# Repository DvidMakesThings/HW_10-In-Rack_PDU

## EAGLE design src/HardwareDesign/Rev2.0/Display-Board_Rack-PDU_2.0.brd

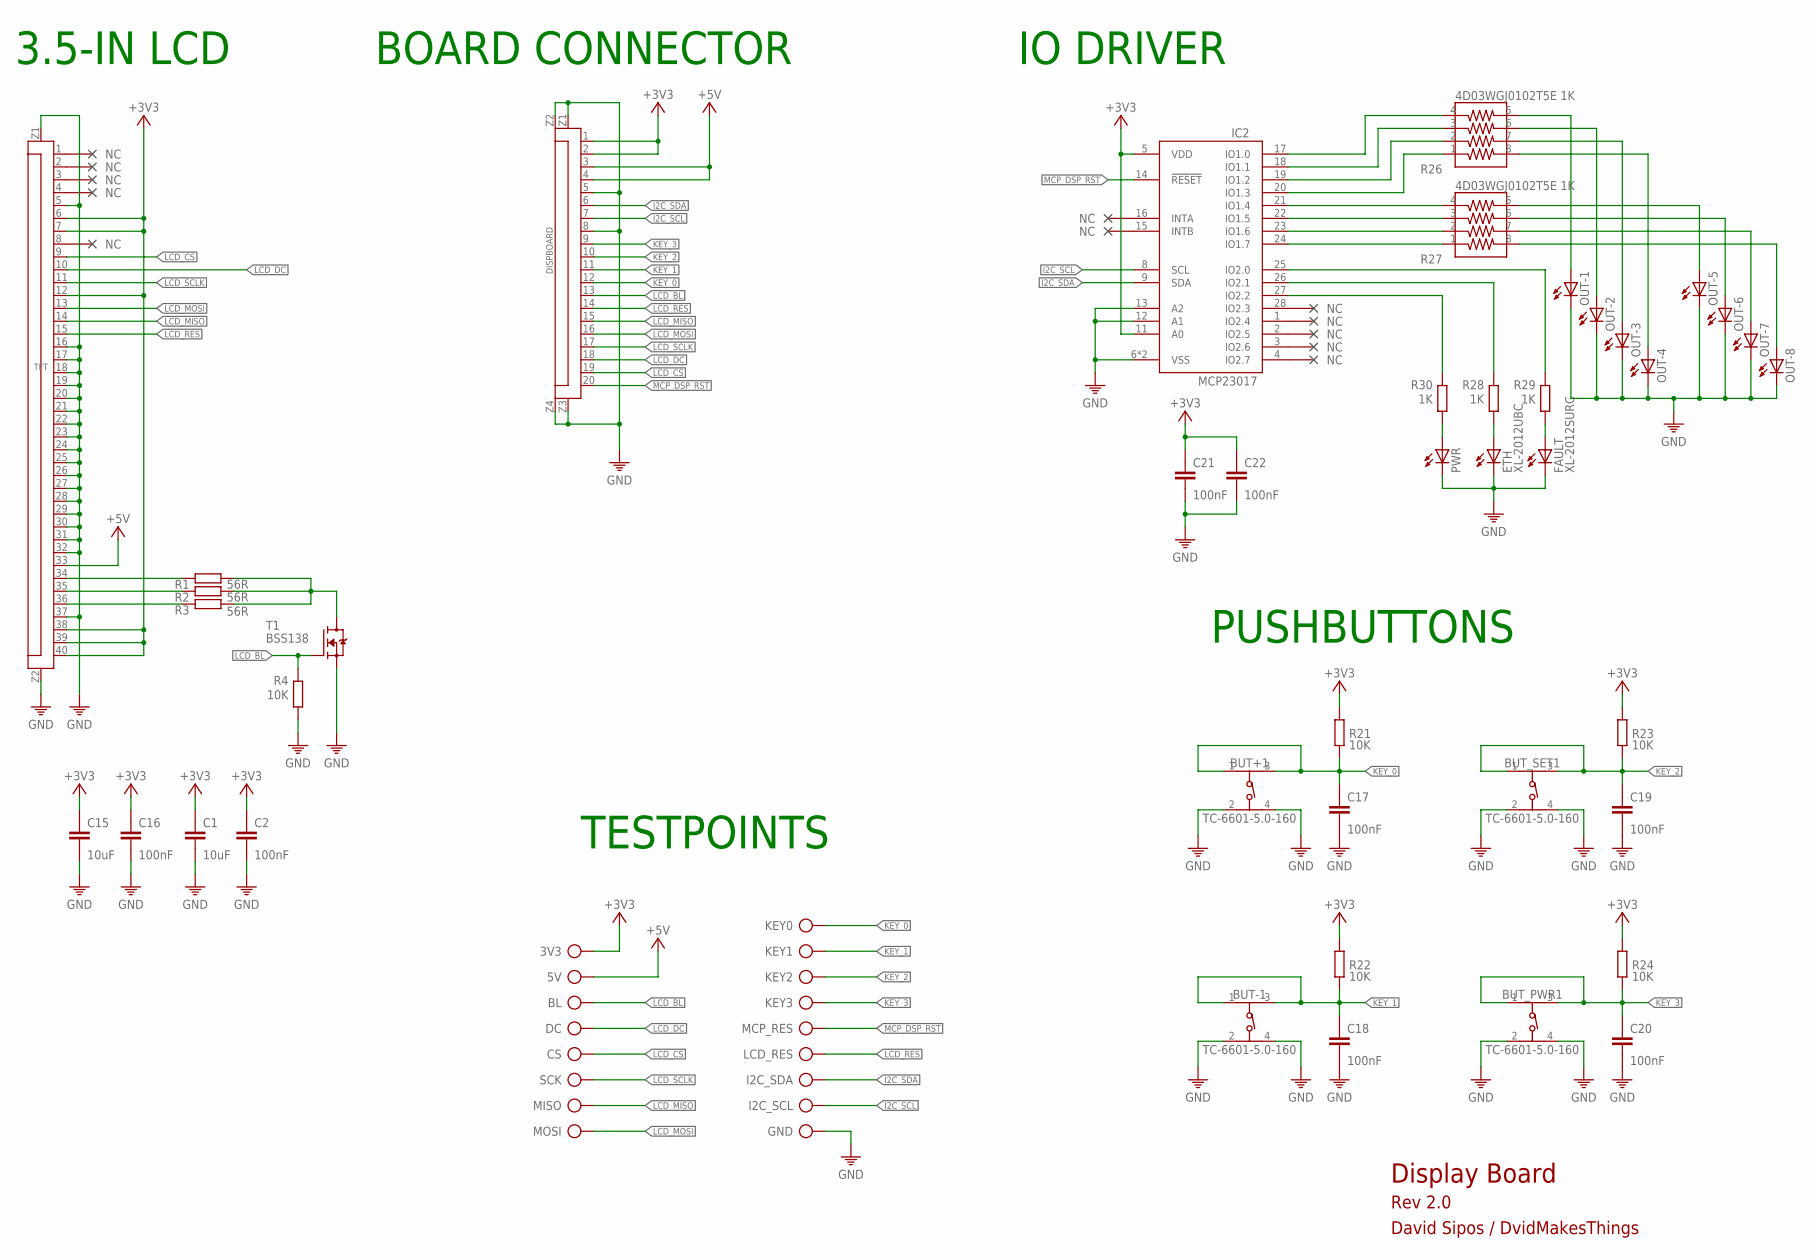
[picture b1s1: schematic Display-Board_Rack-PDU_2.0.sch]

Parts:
3V3, 5V: TP
BL: TP
BUT+1: TC-6601-5.0-160; 430182043816
BUT-1: TC-6601-5.0-160; 430182043816
BUT_PWR1: TC-6601-5.0-160; 430182043816
BUT_SET1: TC-6601-5.0-160; 430182043816
C1, C15: 10uF; C0402
C2, C16, C17, C18, C19, C20, C21, C22: 100nF; C0402
CS: TP
DC: TP
DISPBOARD: FPC20-H; FPC20
ETH: XL-2012UBC; CHIP-LED0805
FAULT: XL-2012SURC; CHIP-LED0805
GND: TP
I2C_SCL, I2C_SDA: TP
IC2: MCP23017-E/ML; QFN28[6X6]ML
KEY0, KEY1, KEY2, KEY3: TP
LCD_RES: TP
MCP_RES: TP
MISO: TP
MOSI: TP
OUT-1, OUT-2, OUT-3, OUT-4, OUT-5, OUT-6, OUT-7, OUT-8: LEDCHIP-LED0805; CHIP-LED0805
PWR: LEDCHIP-LED0805; CHIP-LED0805
R1, R2, R3: 56R; 0402
R4, R21, R22, R23, R24: 10K; 0402
R26, R27: 4D03WGJ0102T5E 1K; 742C083103JP
R28, R29, R30: 1K; 0402
SCK: TP
T1: BSS138; SOT23
TFT: FPC40-HD; FPC40_3.5TFT

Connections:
+3V3: 3V3.TP, C1.1, C2.1, C15.1, C16.1, C21.1, C22.1, DISPBOARD.1, DISPBOARD.2, IC2.5 (VDD), IC2.11 (A0), R21.1, R22.1, R23.1, R24.1, TFT.6, TFT.7, TFT.12, TFT.38, TFT.39, TFT.40
+5V: 5V.TP, DISPBOARD.3, DISPBOARD.4, TFT.33
GND: BUT+1.2, BUT+1.4, BUT-1.2, BUT-1.4, BUT_PWR1.2, BUT_PWR1.4, BUT_SET1.2, BUT_SET1.4, C1.2, C2.2, C15.2, C16.2, C17.2, C18.2, C19.2, C20.2, C21.2, C22.2, DISPBOARD.5, DISPBOARD.8, DISPBOARD.Z1, DISPBOARD.Z2, DISPBOARD.Z3, DISPBOARD.Z4, ETH.C, FAULT.C, GND.TP, IC2.6 (VSS), IC2.12 (A1), IC2.13 (A2), IC2.PAD (VSS), OUT-1.C, OUT-2.C, OUT-3.C, OUT-4.C, OUT-5.C, OUT-6.C, OUT-7.C, OUT-8.C, PWR.C, R4.2, T1.2 (S), TFT.5, TFT.16, TFT.17, TFT.18, TFT.19, TFT.20, TFT.21, TFT.22, TFT.23, TFT.24, TFT.25, TFT.26, TFT.27, TFT.28, TFT.29, TFT.30, TFT.31, TFT.32, TFT.37, TFT.Z1, TFT.Z2
I2C0_SCL: DISPBOARD.7, I2C_SCL.TP, IC2.8 (SCL)
I2C0_SDA: DISPBOARD.6, I2C_SDA.TP, IC2.9 (SDA)
KEY_0: BUT+1.1, BUT+1.3, C17.1, DISPBOARD.12, KEY0.TP, R21.2
KEY_1: BUT-1.1, BUT-1.3, C18.1, DISPBOARD.11, KEY1.TP, R22.2
KEY_2: BUT_SET1.1, BUT_SET1.3, C19.1, DISPBOARD.10, KEY2.TP, R23.2
KEY_3: BUT_PWR1.1, BUT_PWR1.3, C20.1, DISPBOARD.9, KEY3.TP, R24.2
LCD_BL: BL.TP, DISPBOARD.13, R4.1, T1.1 (G)
LCD_CS: CS.TP, DISPBOARD.19, TFT.9
LCD_DC: DC.TP, DISPBOARD.18, TFT.10
LCD_MISO: DISPBOARD.15, MISO.TP, TFT.14
LCD_MOSI: DISPBOARD.16, MOSI.TP, TFT.13
LCD_RES: DISPBOARD.14, LCD_RES.TP, TFT.15
LCD_SCLK: DISPBOARD.17, SCK.TP, TFT.11
MCP_LCD_RST: DISPBOARD.20, IC2.14 (!RESET), MCP_RES.TP
unnamed: R2.2, TFT.35
unnamed: R3.2, TFT.36
unnamed: R1.1, R2.1, R3.1, T1.3 (D)
unnamed: R1.2, TFT.34
unnamed: IC2.26 (IO2.1), R28.1
unnamed: IC2.27 (IO2.2), R30.1
unnamed: IC2.25 (IO2.0), R29.1
unnamed: IC2.17 (IO1.0), R26.4
unnamed: IC2.18 (IO1.1), R26.3
unnamed: IC2.19 (IO1.2), R26.2
unnamed: IC2.20 (IO1.3), R26.1
unnamed: IC2.21 (IO1.4), R27.4
unnamed: IC2.22 (IO1.5), R27.3
unnamed: IC2.23 (IO1.6), R27.2
unnamed: IC2.24 (IO1.7), R27.1
unnamed: OUT-1.A, R26.5
unnamed: OUT-2.A, R26.6
unnamed: OUT-3.A, R26.7
unnamed: OUT-4.A, R26.8
unnamed: OUT-5.A, R27.5
unnamed: OUT-6.A, R27.6
unnamed: OUT-7.A, R27.7
unnamed: OUT-8.A, R27.8
unnamed: FAULT.A, R29.2
unnamed: ETH.A, R28.2
unnamed: PWR.A, R30.2

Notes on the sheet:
BOARD CONNECTOR
3.5-IN LCD
PUSHBUTTONS
IO DRIVER
Display Board
Rev 2.0
David Sipos / DvidMakesThings
TESTPOINTS

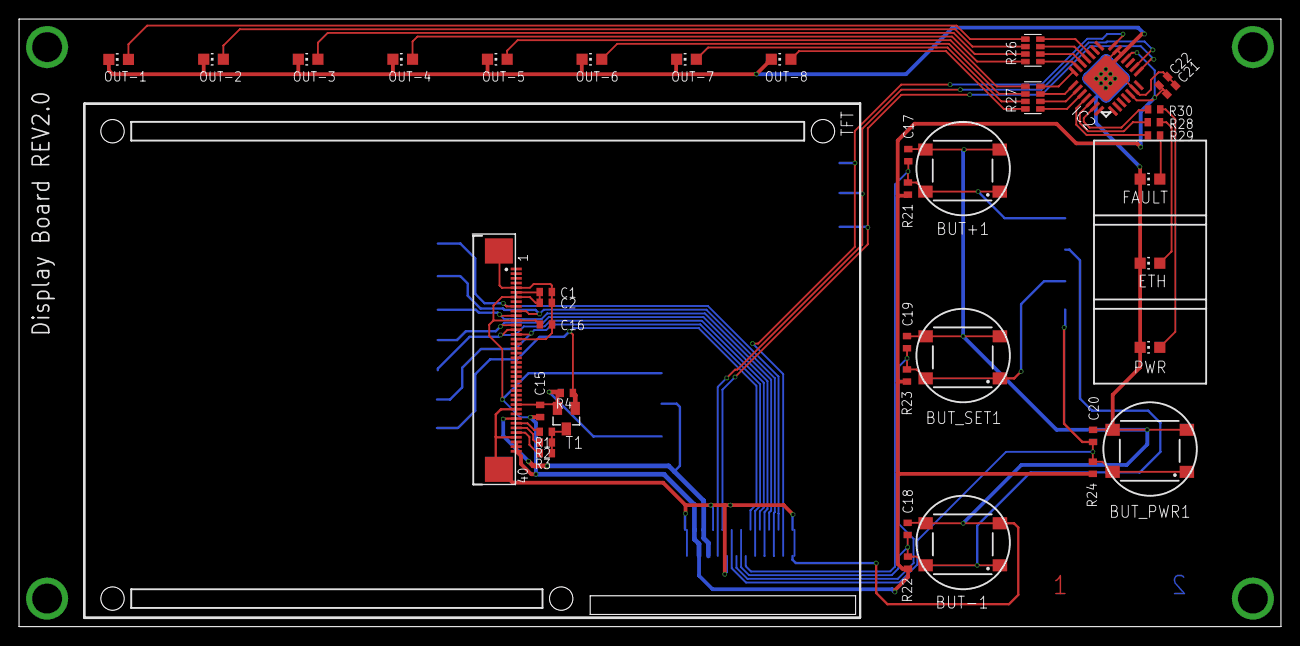
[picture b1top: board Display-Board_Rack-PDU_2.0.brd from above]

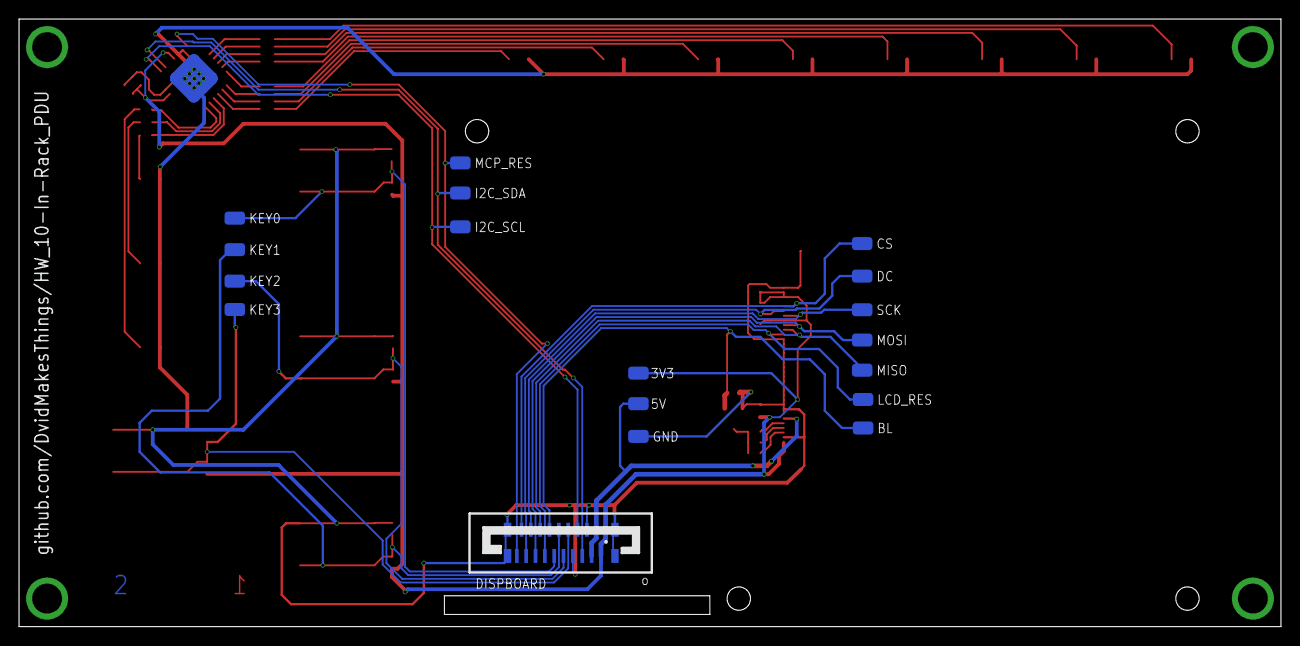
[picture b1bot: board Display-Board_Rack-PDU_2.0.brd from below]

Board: 2 copper layers, 135.0 x 65.0 mm, 60 parts (18 on the bottom side), 43 nets.

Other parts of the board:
U$1: 2-LAYER

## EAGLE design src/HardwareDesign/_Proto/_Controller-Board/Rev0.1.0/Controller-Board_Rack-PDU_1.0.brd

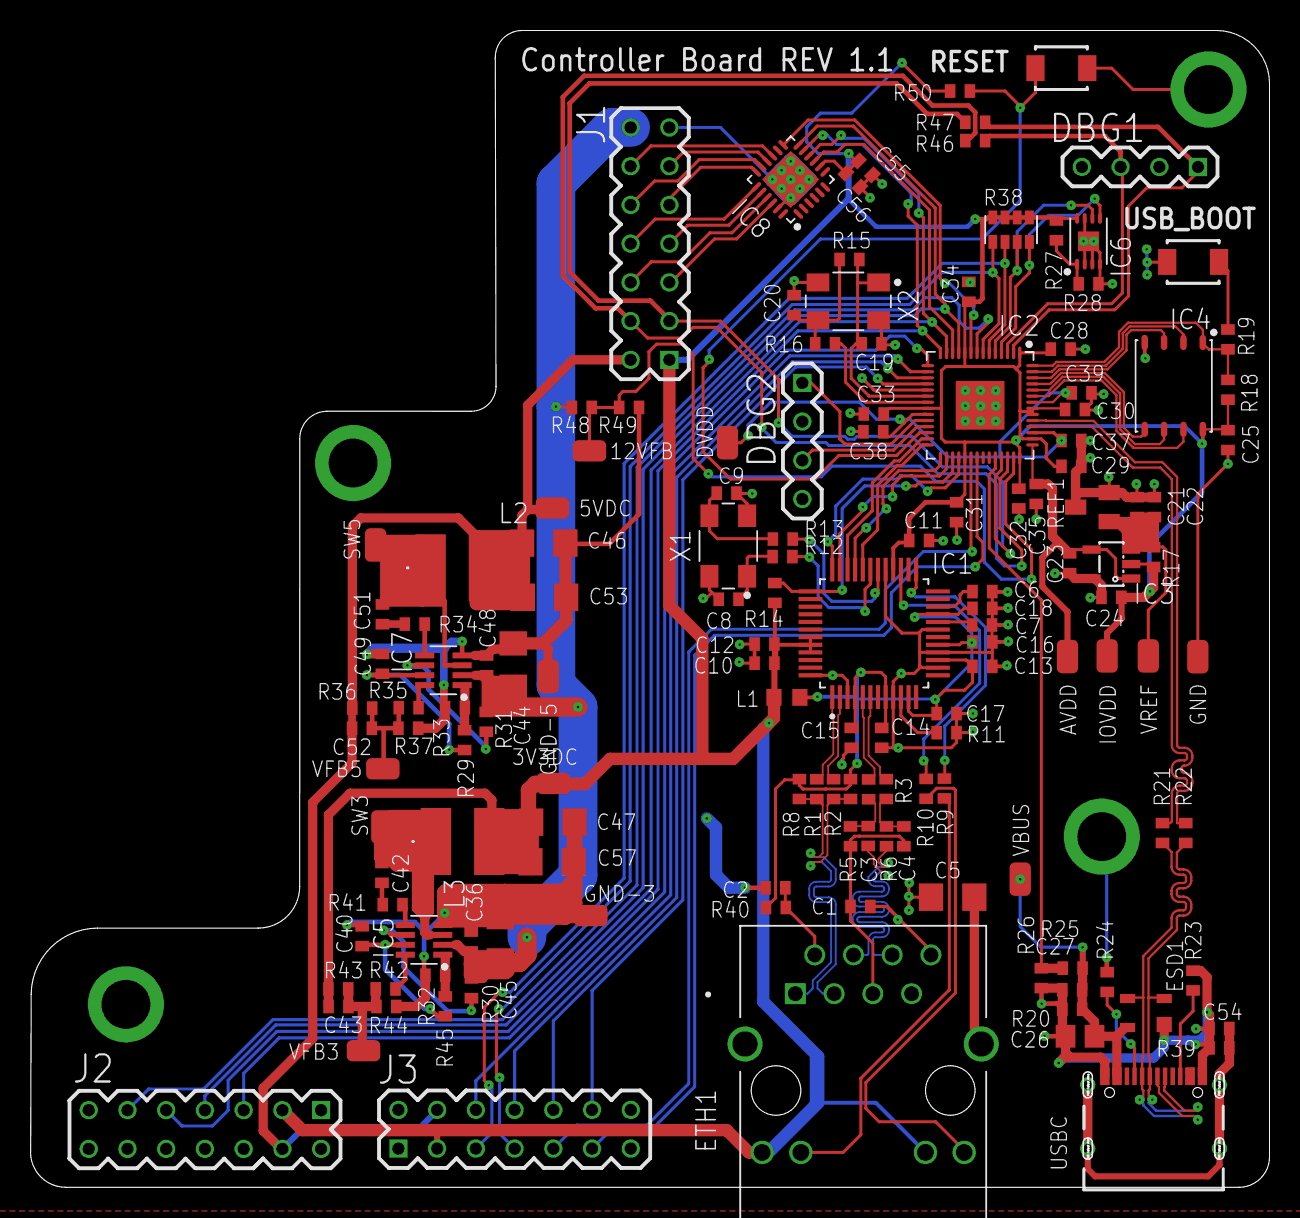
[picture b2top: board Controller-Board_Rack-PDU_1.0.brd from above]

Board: 4 copper layers, 81.3 x 75.9 mm, 144 parts (0 on the bottom side), 106 nets.

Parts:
3V3DC, 5VDC, 12VFB: TP
AVDD: TP
C1, C6, C10, C11, C12, C13, C14, C15, C16, C17, C18, C22, C23, C24, C25, C28, C29, C30, C31, C32, C33, C34, C35, C37, C38, C39, C55, C56: 100nF; C0402
C2: 22nF; C0402
C3, C4: 6.8nF; C0402
C5: C1206C102KGRACTM; C1206
C7: 4.7uF; C0402
C8, C9: 18pF; C0402
C19, C20: 15pF; C0402
C21: 1uF; C0402
C26: 10uF; 0805
C27, C36, C40, C42, C48, C49, C51: 100nF; 0402
C43, C52: 33pF; 0402
C44, C45: CL31A226KAHNNNE - 22uF 25V; C1206
C46, C47, C53, C57: CL31A226KPHNNNE - 22uF - 10V; C1206
C54: 4.7nF; 0402
DBG1, DBG2: 1X4
DVDD: TP
ESD1: SP0503BAHTG-ES; SOT143
ETH1: SI-60118-F; RJ45-CAT5
GND: TP
GND-3, GND-5: TP
IC1: W5500; LQFP48
IC2: RP2040; QFN40P700X700X100-57T510
IC3: MCP6001R; SOT23-5
IC4: W25Q128JVPIQ; SON127P600X500X75-8N
IC5: MP2315S; SOT65P280X110-8N
IC6: CAT24C256HU4IGT3; SON50P300X200X50-9T130X140N
IC7: MP2315GJ-Z; SOT65P280X110-8N
IC8: MCP23S18-E/MJ; QFN50P400X400X100-25T265
IOVDD: TP
J1, J2, J3: 2X7
L1: BLM18EG221TN1D; 0603
L2: 4.9uH; SRR5228A
L3: 4.2uH; SRR5228A
R1, R2, R3, R4: 3.3R; 0402
R5, R6: 49.9R; C0402
R7, R8: 49.9R; 0402
R9, R10, R40: 470R; 0402
R11: 12.4K 1%; 0402
R12, R15, R46, R47: 0R; 0402
R13, R39: 1M; 0402
R14, R17, R27, R28: 4.7K; 0402
R16, R19: 1K; 0402
R18: DNI; 0402
R20: 2.2K 1%; 0402
R21, R22: 27R; 0402
R23, R24: 5.1K; 0402
R25, R26, R49, R50: 10K; 0402
R29, R45, R48: 100K; 0402
R30, R31: 499K; 0402
R32, R37: 7.5K; 0402
R33: 9.09K; 0402
R34, R41: 10R; 0402
R35: 20K; 0402
R36, R43: 40.2K; 0402
R38: 4D03WGJ0332T5E; 742C083103JP
R42: 33K; 0402
R44: 12.7K; 0402
REF1: LM4040BXX; SOT23
RESET: B3U-1000P-B; SWITCH-OMRON_B3U-1000P
SW3, SW5: TP
USBC: USB-TYPE-C-018; 629722000214
USB_BOOT: B3U-1000P-B; SWITCH-OMRON_B3U-1000P
VBUS: TP
VFB3, VFB5: TP
VREF: TP
X1: XC53M4-25.000-F18NJDTL; OSCCC500X320X130
X2: K5A1200015304P; OSCCC500X320X130

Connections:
!ACT: IC1.27, R10.1
!INT: IC1.36, IC2.32
!LINK: IC1.25, R9.1
!QSPI_SS: IC2.56, IC4.1, R18.1, R19.2
!RST: IC1.37, IC2.31, R14.1
!SPI0_CS: IC1.32, IC2.28
!SPI1_CS: IC2.12, IC8.9
!SPI1_CS_S: IC2.8, J2.11
+1V1: C37.1, C38.1, C39.1, DVDD.TP, IC2.23, IC2.45, IC2.50
+3V3: 3V3DC.TP, C10.1, C11.1, C12.1, C24.1, C25.1, C28.1, C29.1, C30.1, C31.1, C32.1, C33.1, C34.1, C43.1, C47.1, C55.1, C56.1, C57.1, ETH1.9, ETH1.11, IC1.28, IC1.43, IC1.44, IC1.45, IC2.1, IC2.10, IC2.22, IC2.33, IC2.42, IC2.44, IC2.48, IC2.49, IC3.2, IC4.8, IC6.8, IC8.8, IOVDD.TP, J1.1, J2.3, J3.3, L1.1, L3.2, R14.2, R17.2, R18.2, R27.2, R38.5, R38.6, R38.7, R38.8, R43.1, R50.1
+3V3_A: C13.1, C14.1, C15.1, C16.1, C17.1, C18.1, IC1.4, IC1.8, IC1.11, IC1.15, IC1.17, IC1.21, L1.2, R7.2, R8.2, R40.2
+5V: 5VDC.TP, C46.1, C52.1, C53.1, J1.2, J2.4, J3.4, L2.2, R36.1
+12V: C36.1, C44.1, C45.1, C48.1, IC5.2, IC7.2, J1.14, R30.1, R31.1, R48.2
AVDD: AVDD.TP, C23.1, C35.1, IC2.43, IC3.1, IC3.4
CC1: R24.1, USBC.A5
CC2: R23.1, USBC.B5
CHASSIS: C5.2, ETH1.S1, ETH1.S2
DIO_RESET: IC2.9, IC8.13
DP_N: ESD1.3, R21.1, USBC.A7, USBC.B7
DP_P: ESD1.2, R22.1, USBC.A6, USBC.B6
DSP_RES: IC2.34, J3.9
EXP_RST: IC2.35, J3.11
GND: C1.2, C2.2, C5.1, C6.2, C7.2, C8.2, C9.2, C10.2, C11.2, C12.2, C13.2, C14.2, C15.2, C16.2, C17.2, C18.2, C19.2, C20.2, C21.2, C22.2, C23.2, C24.2, C25.2, C26.2, C27.2, C28.2, C29.2, C30.2, C31.2, C32.2, C33.2, C34.2, C35.2, C36.2, C37.2, C38.2, C39.2, C40.2, C44.2, C45.2, C46.2, C47.2, C48.2, C49.2, C53.2, C54.2, C55.2, C56.2, C57.2, DBG1.2, DBG1.4, DBG2.2, DBG2.4, ESD1.1, ETH1.8, GND.TP, GND-3.TP, GND-5.TP, IC1.3, IC1.9, IC1.14, IC1.16, IC1.19, IC1.29, IC1.48, IC2.19, IC2.57, IC3.5, IC4.4, IC5.4, IC6.2, IC6.3, IC6.4, IC6.7, IC6.9, IC7.4, IC8.23, IC8.25, J1.13, J2.1, J2.2, J2.13, J2.14, J3.1, J3.2, J3.13, J3.14, R11.1, R20.2, R23.2, R24.2, R26.2, R28.1, R32.2, R33.2, R37.2, R39.2, R44.2, R49.1, REF1.2, REF1.3, RESET.2, USBC.A1, USBC.A12, USBC.B1, USBC.B12, USB_BOOT.2, X1.2, X1.4, X2.2, X2.4
I2C0_SCL: IC2.7, J3.7, R38.1
I2C0_SDA: IC2.6, J3.5, R38.2
I2C1_SCL: IC2.5, IC6.6, R38.3
I2C1_SDA: IC2.4, IC6.5, R38.4
I_MEA/TX: IC2.40, J1.4, R46.1
KEY_0: IC2.15, J3.6
KEY_1: IC2.16, J3.8
KEY_2: IC2.17, J3.10
KEY_3: IC2.18, J3.12
unnamed: IC1.10, R11.2
unnamed: ETH1.10, R9.2
unnamed: ETH1.12, R10.2
unnamed: C6.1, IC1.22
unnamed: C7.1, IC1.20
unnamed: C8.1, R12.1, X1.1
unnamed: C9.1, R13.1, X1.3
unnamed: IC1.31, R12.2
unnamed: IC1.30, R13.2
unnamed: IC5.5, R41.2
unnamed: IC5.1, R32.1, R45.2
unnamed: IC7.1, R29.2, R33.1
unnamed: C20.1, R15.2, R16.1, X2.3
unnamed: IC7.6, R31.2
unnamed: C49.1, IC7.7, R29.1
unnamed: IC2.26, R50.2, RESET.1
unnamed: IC5.8, R42.1
unnamed: C42.2, IC5.3, L3.1, SW3.TP
unnamed: C42.1, R41.1
unnamed: IC6.1, R27.1, R28.2
unnamed: C43.2, R42.2, R43.2, R44.1, VFB3.TP
unnamed: IC5.6, R30.2
unnamed: C40.1, IC5.7, R45.1
unnamed: IC7.5, R34.2
unnamed: IC7.8, R35.1
unnamed: C51.2, IC7.3, L2.1, SW5.TP
unnamed: C51.1, R34.1
unnamed: C52.2, R35.2, R36.2, R37.1, VFB5.TP
PWR_DETECT: 12VFB.TP, IC2.41, R48.1, R49.2
QSPI_SCLK: IC2.52, IC4.6
QSPI_SD0: IC2.53, IC4.5
QSPI_SD1: IC2.55, IC4.2
QSPI_SD2: IC2.54, IC4.3
QSPI_SD3: IC2.51, IC4.7
RCT: C1.1, ETH1.5, R5.1, R6.1
RDC_RD_N: C3.1, R4.2, R5.2
RDC_RD_P: C4.1, R3.2, R6.2
RD_N: C3.2, ETH1.6
RD_P: C4.2, ETH1.4
REL_0: IC8.15, J1.12
REL_1: IC8.16, J1.11
REL_2: IC8.17, J1.10
REL_3: IC8.18, J1.9
REL_4: IC8.19, J1.8
REL_5: IC8.20, J1.7
REL_6: IC8.21, J1.6
REL_7: IC8.22, J1.5
RP_XI: C19.1, IC2.20, R15.1, X2.1
RP_XO: IC2.21, R16.2
RX_RD_N: IC1.5, R4.1
RX_RD_P: IC1.6, R3.1
SPI0_MISO: IC1.34, IC2.27
SPI0_MOSI: IC1.35, IC2.30
SPI0_SCK: IC1.33, IC2.29
SPI1_MISO: IC2.11, IC8.12, J2.7
SPI1_MOSI: IC2.14, IC8.11, J2.5
SPI1_SCK: IC2.13, IC8.10, J2.9
SWCLK: DBG2.1, IC2.24
SWDIO: DBG2.3, IC2.25
TCT: C2.1, ETH1.2, R40.1
TD_N: ETH1.3, R1.2, R8.1
TD_P: ETH1.1, R2.2, R7.1
TX_TD_N: IC1.1, R1.1
TX_TD_P: IC1.2, R2.1
UART0_RX: DBG1.1, IC2.2, R47.2
UART0_TX: DBG1.3, IC2.3, R46.2
USB_BOOT: R19.1, USB_BOOT.1
USB_DP_N: IC2.46, R21.2
USB_DP_P: IC2.47, R22.2
USB_SHIELD: C54.1, R39.1, USBC.S1, USBC.S2, USBC.S3, USBC.S4
VBUS: C26.1, C27.1, ESD1.4, R20.1, R25.1, USBC.A4, USBC.A9, USBC.B4, USBC.B9, VBUS.TP
VREF: C21.1, C22.1, IC3.3, R17.1, REF1.1, VREF.TP
V_MEA/RX: IC2.39, J1.3, R47.1
V_USB: IC2.38, R25.2, R26.1

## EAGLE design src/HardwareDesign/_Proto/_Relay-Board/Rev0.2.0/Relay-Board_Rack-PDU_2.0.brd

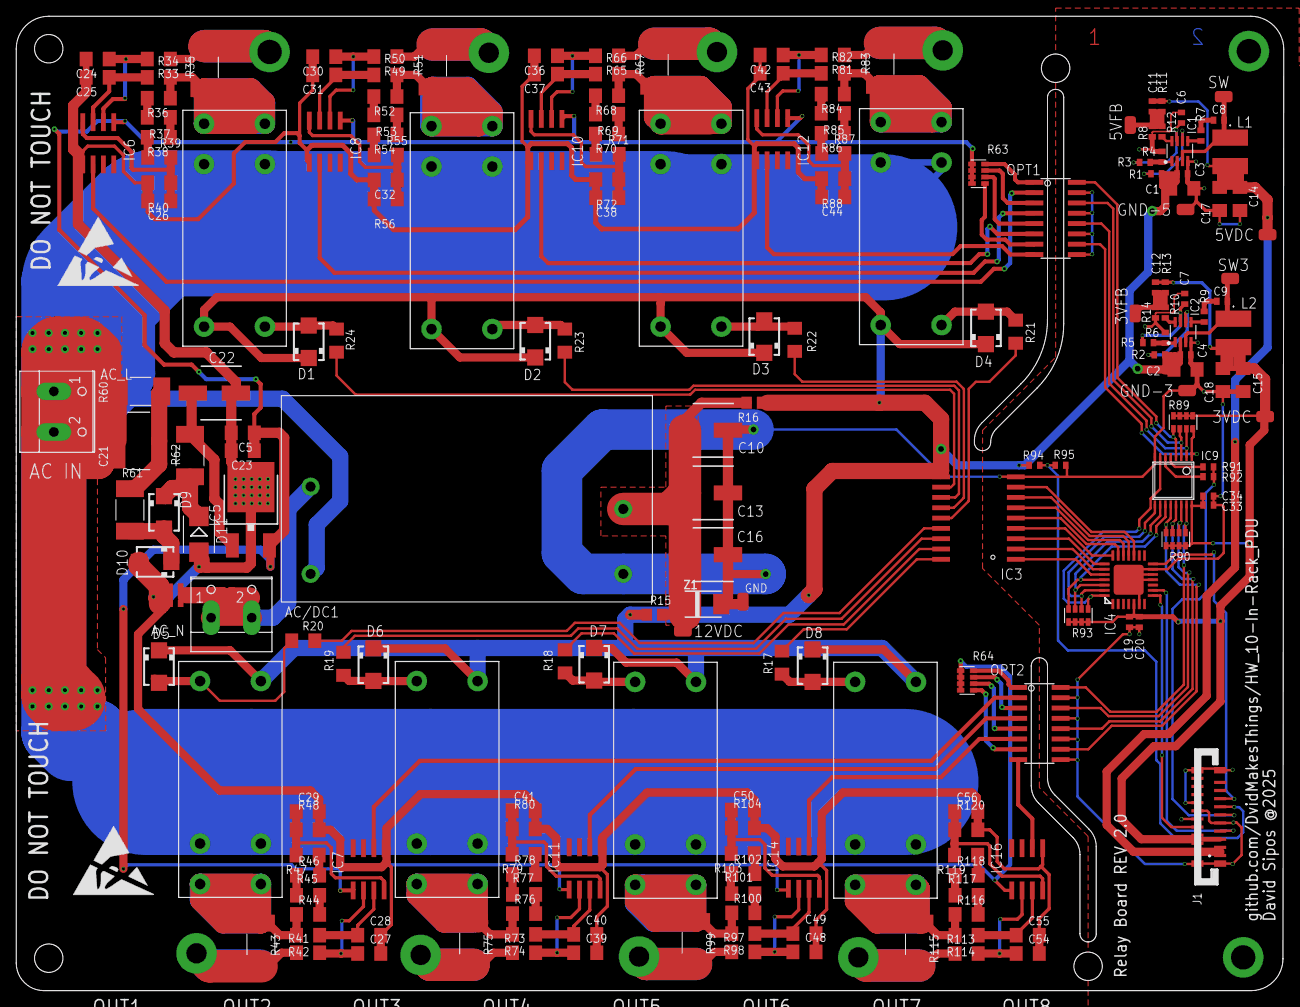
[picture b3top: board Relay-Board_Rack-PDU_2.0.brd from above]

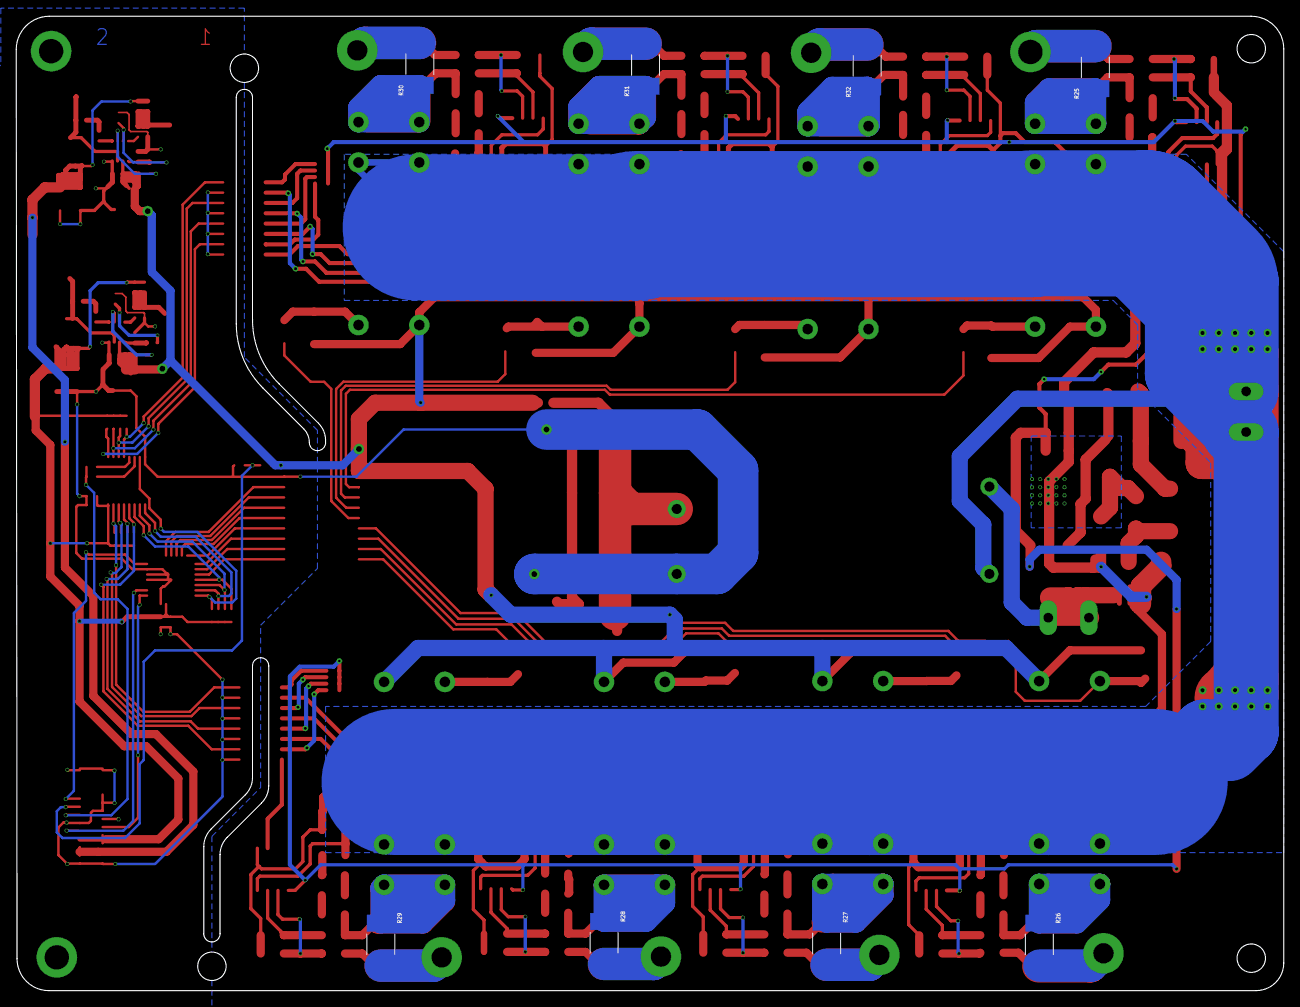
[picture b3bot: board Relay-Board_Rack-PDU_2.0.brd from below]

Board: 2 copper layers, 156.1 x 120.0 mm, 215 parts (8 on the bottom side), 152 nets.

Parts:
3VDC, 3VFB, 5VDC, 5VFB, 12VDC: TP
AC/DC1: IRM_10_12
AC_L: W237-102
AC_N: W237-102
C1, C2: 22uF 25V; C1206
C3, C4, C6, C7, C8, C9: 100nF; 0402
C5, C23: 10uF 16V; C1206
C10, C13, C16: 100uF; 100UF-16V
C11, C12: 33pF; 0402
C14, C15, C17, C18: 22uF - 10V; C1206
C19, C20, C33, C34: 100nF; C0402
C21: 470nF 630V; 2225
C22: 470uF 25V; 100UF-16V
C24, C25, C26, C27, C28, C29, C30, C31, C32, C36, C37, C38, C39, C40, C41, C42, C43, C44, C48, C49, C50, C54, C55, C56: 33nF; C1206
D1: MBRA340T3G; SMA
D2, D3, D4, D5, D6, D7, D8: MBRA340T3; SMA
D9, D10: S1M; SMA
D11: 9.1V 1W; SMB
GND: TP
GND-3, GND-5: TP
IC1: MP2315GJ-Z; SOT65P280X110-8N
IC2: MP2315S; SOT65P280X110-8N
IC3: ULN2803A; SO18
IC4: MCP23017-E/ML; QFN28[6X6]ML
IC5: BA50BC0FP-E2; DPAK
IC6, IC7, IC8, IC10, IC11, IC12, IC14, IC16: HLW8032; SO8
IC9: SN74HC151PWR; TSSOP16
J1: FPC20-H; FPC20
K1, K2, K3, K4, K5, K6, K7, K8: G2RL-1A-E_DC12; RELAY_G2RL-1A-E_DC5_OMR
L1: 4.9uH; SRR5228A
L2: 4.2uH; SRR5228A
OPT1, OPT2: TLP291-4; SO16
R1, R2: 499K; 0402
R3, R5, R94: 100K; 0402
R4: 9.09K; 0402
R6, R12: 7.5K; 0402
R7, R9: 10R; 0402
R8: 20K; 0402
R10: 33K; 0402
R11, R13: 40.2K; 0402
R14: 12.7K; 0402
R15, R16: 0R; 0805
R17, R18, R19, R20, R21, R22, R23, R24: 330R 1W; 1206
R25, R26, R27, R28, R29, R30, R31, R32, R35, R43, R51, R67, R75, R83, R99, R115: 0.002R 1%; 2512
R33, R34, R40, R41, R42, R48, R49, R50, R56, R65, R66, R72, R73, R74, R80, R81, R82, R88, R97, R98, R104, R113, R114, R120: 1K 1%; 1206
R36, R37, R38, R39, R44, R45, R46, R47, R52, R53, R54, R55, R68, R69, R70, R71, R76, R77, R78, R79, R84, R85, R86, R87, R100, R101, R102, R103, R116, R117, R118, R119: 470K; 1206
R57, R58, R59: JP; 0402
R60: 470K 1W; 2512
R61, R62: 100R 1W; 2512
R63, R64, R89, R90: 4x1K 1206; 742C083103JP
R91, R92: 0R; 0402
R93: 4x10K 1206; 742C083103JP
R95: 10K; 0402
SW, SW3: TP
U$1, U$2: ESD_10.00
U$3: 2-LAYER
Z1: SMAJ15A; SUPRESSOR_SMAJ

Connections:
5VFB: 5VFB.TP, C11.2, R8.2, R11.2, R12.1
+3V3: 3VDC.TP, C12.1, C15.1, C18.1, C19.1, C20.1, C33.1, C34.1, IC4.5, IC9.16, J1.4, J1.5, J1.6, L2.2, R13.1, R89.5, R89.6, R89.7, R89.8, R90.5, R90.6, R90.7, R90.8, R93.5, R93.6, R93.7, R93.8
+5V: 5VDC.TP, C11.1, C14.1, C17.1, J1.1, J1.2, J1.3, L1.2, R11.1
+5V_MEA: C5.1, C23.1, IC5.3, IC6.1, IC7.1, IC8.1, IC10.1, IC11.1, IC12.1, IC14.1, IC16.1, R63.1, R63.2, R63.3, R63.4, R64.1, R64.2, R64.3, R64.4
+12V: C1.1, C2.1, C3.1, C4.1, D1.C, D2.C, D3.C, D4.C, D5.C, D6.C, D7.C, D8.C, IC1.2, IC2.2, IC3.10, K1.8, K2.8, K3.8, K4.8, K5.8, K6.8, K7.8, K8.8, R1.1, R2.1, R15.1, R16.1, R94.2
+12V_MEA: J1.13, R94.1, R95.2
AC_L: AC/DC1.AC_L, AC_L.1, AC_L.2, C21.1, K1.3, K1.6, K2.3, K2.6, K3.3, K3.6, K4.3, K4.6, K5.3, K5.6, K6.3, K6.6, K7.3, K7.6, K8.3, K8.6, R60.1
AC_N: AC/DC1.AC_N, AC_N.1, AC_N.2, R57.1, R58.1, R59.1
AGND: C5.2, C22.2, C23.2, C24.2, C25.2, C26.2, C27.2, C28.2, C29.2, C30.2, C31.2, C32.2, C36.2, C37.2, C38.2, C39.2, C40.2, C41.2, C42.2, C43.2, C44.2, C48.2, C49.2, C50.2, C54.2, C55.2, C56.2, D10.A, D11.A, IC5.4, IC6.5, IC7.5, IC8.5, IC10.5, IC11.5, IC12.5, IC14.5, IC16.5, R40.2, R48.2, R56.2, R57.2, R58.2, R59.2, R72.2, R80.2, R88.2, R104.2, R120.2
C13_IN1: R25.2, R33.1, R35.2
C13_IN2: R32.2, R49.1, R51.2
C13_IN3: R31.2, R65.1, R67.2
C13_IN4: R30.2, R81.1, R83.2
C13_IN5: R26.2, R41.1, R43.2
C13_IN6: R27.2, R73.1, R75.2
C13_IN7: R28.2, R97.1, R99.2
C13_IN8: R29.2, R113.1, R115.2
GND: AC/DC1.-V, C1.2, C2.2, C3.2, C4.2, C6.2, C7.2, C10.2, C13.2, C14.2, C15.2, C16.2, C17.2, C18.2, C19.2, C20.2, C33.2, C34.2, GND.TP, GND-3.TP, GND-5.TP, IC1.4, IC2.4, IC3.9, IC4.6, IC4.11, IC4.12, IC4.13, IC4.PAD, IC9.8, J1.9, J1.12, J1.14, J1.16, J1.Z1, J1.Z2, J1.Z3, J1.Z4, OPT1.9, OPT1.11, OPT1.13, OPT1.15, OPT2.9, OPT2.11, OPT2.13, OPT2.15, R4.2, R6.2, R12.2, R14.2, R95.1, Z1.A
I2C_SCL: IC4.8, J1.8
I2C_SDA: IC4.9, J1.7
MCP_REL_RST: IC4.14, J1.15
MUX_A: IC4.25, IC9.11, R93.4
MUX_B: IC4.26, IC9.10, R93.3
MUX_C: IC4.27, IC9.9, R93.2
MUX_EN: IC4.28, IC9.7, R93.1
unnamed: IC9.5, R91.1
unnamed: 12VDC.TP, AC/DC1.+V, C10.1, C13.1, C16.1, R15.2, R16.2, Z1.C
unnamed: C21.2, R60.2, R61.1
unnamed: IC3.14, R21.1
unnamed: OPT1.1, R63.8
unnamed: IC3.11, R24.1
unnamed: IC3.12, R23.1
unnamed: IC3.13, R22.1
unnamed: OPT1.3, R63.7
unnamed: IC3.15, R20.1
unnamed: IC3.16, R19.1
unnamed: C24.1, IC6.2, R33.2
unnamed: IC3.17, R18.1
unnamed: IC1.5, R7.2
unnamed: IC3.18, R17.1
unnamed: IC1.8, R8.1
unnamed: OPT1.5, R63.6
unnamed: C8.1, R7.1
unnamed: IC1.6, R1.2
unnamed: D9.A, D10.C, R61.2
unnamed: C6.1, IC1.7, R3.1
unnamed: C25.1, IC6.3, R34.2
unnamed: OPT1.7, R63.5
unnamed: IC9.6, R92.1
unnamed: C22.1, IC5.1, R62.2
unnamed: D9.C, D11.C, R62.1
unnamed: R36.2, R37.1
unnamed: R37.2, R38.1
unnamed: R38.2, R39.1
unnamed: C26.1, IC6.4, R39.2, R40.1
unnamed: C27.1, IC7.2, R41.2
unnamed: C28.1, IC7.3, R42.2
unnamed: R44.2, R45.1
unnamed: R45.2, R46.1
unnamed: R46.2, R47.1
unnamed: C29.1, IC7.4, R47.2, R48.1
unnamed: OPT2.1, R64.8
unnamed: IC2.5, R9.2
unnamed: IC2.8, R10.1
unnamed: OPT2.3, R64.7
unnamed: C9.1, R9.1
unnamed: 3VFB.TP, C12.2, R10.2, R13.2, R14.1
unnamed: IC2.6, R2.2
unnamed: C7.1, IC2.7, R5.1
unnamed: IC1.1, R3.2, R4.1
unnamed: IC2.1, R5.2, R6.1
unnamed: C30.1, IC8.2, R49.2
unnamed: C31.1, IC8.3, R50.2
unnamed: R52.2, R53.1
unnamed: R53.2, R54.1
unnamed: R54.2, R55.1
unnamed: C32.1, IC8.4, R55.2, R56.1
unnamed: OPT2.5, R64.6
unnamed: OPT2.7, R64.5
unnamed: C36.1, IC10.2, R65.2
unnamed: C37.1, IC10.3, R66.2
unnamed: R68.2, R69.1
unnamed: R69.2, R70.1
unnamed: R70.2, R71.1
unnamed: C38.1, IC10.4, R71.2, R72.1
unnamed: C39.1, IC11.2, R73.2
unnamed: C40.1, IC11.3, R74.2
unnamed: R76.2, R77.1
unnamed: R77.2, R78.1
unnamed: R78.2, R79.1
unnamed: C41.1, IC11.4, R79.2, R80.1
unnamed: C42.1, IC12.2, R81.2
unnamed: C43.1, IC12.3, R82.2
unnamed: R84.2, R85.1
unnamed: R85.2, R86.1
unnamed: R86.2, R87.1
unnamed: C44.1, IC12.4, R87.2, R88.1
unnamed: C48.1, IC14.2, R97.2
unnamed: C49.1, IC14.3, R98.2
unnamed: R100.2, R101.1
unnamed: R101.2, R102.1
unnamed: R102.2, R103.1
unnamed: C50.1, IC14.4, R103.2, R104.1
unnamed: C54.1, IC16.2, R113.2
unnamed: C55.1, IC16.3, R114.2
unnamed: R116.2, R117.1
unnamed: R117.2, R118.1
unnamed: R118.2, R119.1
unnamed: C56.1, IC16.4, R119.2, R120.1
OUT_1: K1.4, K1.5, R25.1, R34.1, R35.1, R36.1
OUT_2: K2.4, K2.5, R32.1, R50.1, R51.1, R52.1
OUT_3: K3.4, K3.5, R31.1, R66.1, R67.1, R68.1
OUT_4: K4.4, K4.5, R30.1, R82.1, R83.1, R84.1
OUT_5: K5.4, K5.5, R26.1, R42.1, R43.1, R44.1
OUT_6: K6.4, K6.5, R27.1, R74.1, R75.1, R76.1
OUT_7: K7.4, K7.5, R28.1, R98.1, R99.1, R100.1
OUT_8: K8.4, K8.5, R29.1, R114.1, R115.1, R116.1
RELAY_1: D1.A, K1.1, R24.2
RELAY_2: D2.A, K2.1, R23.2
RELAY_3: D3.A, K3.1, R22.2
RELAY_4: D4.A, K4.1, R21.2
RELAY_5: D5.A, K5.1, R20.2
RELAY_6: D6.A, K6.1, R19.2
RELAY_7: D7.A, K7.1, R18.2
RELAY_8: D8.A, K8.1, R17.2
REL_0: IC3.8, IC4.17
REL_1: IC3.7, IC4.18
REL_2: IC3.6, IC4.19
REL_3: IC3.5, IC4.20
REL_4: IC3.4, IC4.21
REL_5: IC3.3, IC4.22
REL_6: IC3.2, IC4.23
REL_7: IC3.1, IC4.24
SW3: C9.2, IC2.3, L2.1, SW3.TP
SW5: C8.2, IC1.3, L1.1, SW.TP
TX_CH1: IC6.6, OPT1.2
TX_CH2: IC8.6, OPT1.4
TX_CH3: IC10.6, OPT1.6
TX_CH4: IC12.6, OPT1.8
TX_CH5: IC7.6, OPT2.2
TX_CH6: IC11.6, OPT2.4
TX_CH7: IC14.6, OPT2.6
TX_CH8: IC16.6, OPT2.8
TX_MUX1: IC9.4, OPT1.16, R89.1
TX_MUX2: IC9.3, OPT1.14, R89.2
TX_MUX3: IC9.2, OPT1.12, R89.3
TX_MUX4: IC9.1, OPT1.10, R89.4
TX_MUX5: IC9.15, OPT2.16, R90.1
TX_MUX6: IC9.14, OPT2.14, R90.2
TX_MUX7: IC9.13, OPT2.12, R90.3
TX_MUX8: IC9.12, OPT2.10, R90.4
UART0_TX: J1.11, R91.2, R92.2

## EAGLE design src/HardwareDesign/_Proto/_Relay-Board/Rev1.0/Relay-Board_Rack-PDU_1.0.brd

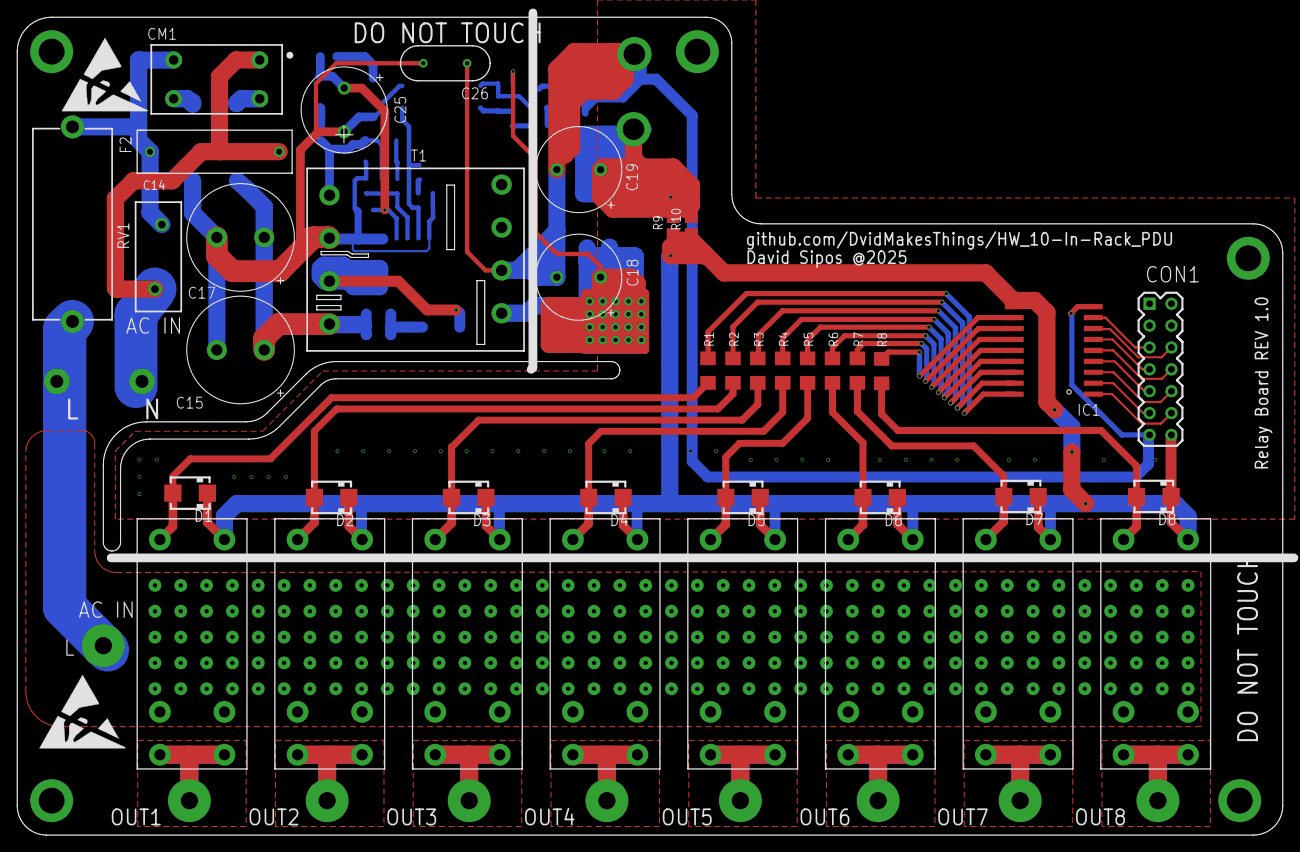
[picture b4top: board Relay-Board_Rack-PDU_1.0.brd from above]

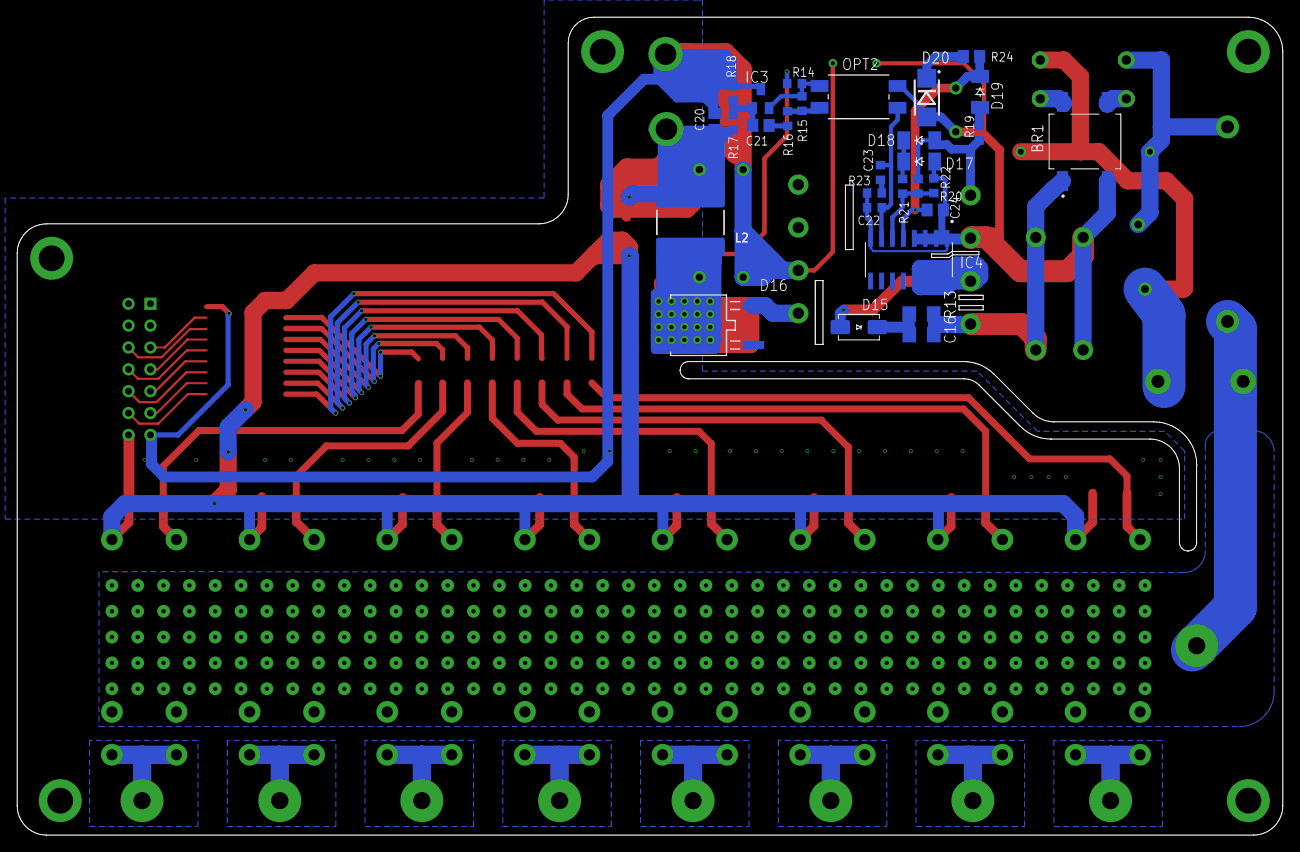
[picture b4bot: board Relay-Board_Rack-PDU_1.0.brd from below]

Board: 2 copper layers, 147.0 x 95.0 mm, 70 parts (29 on the bottom side), 58 nets.

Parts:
BR1: DBLS207G; DIOB_DBLS207G
C14: MP2104K27C3R6LC 100nF 275V; 103-275V
C15, C17: KM150M400G160A 15uF 400V; CAPPRD550W110D1250H2500B
C16: 10nF 1kV; C1206
C18: 470uF 25V; CAPPRD508W65D1000H1100B
C19, C25: 100uF 25V; CAPPRD508W65D1000H1100B
C20: 1uF 25V; C0805
C21: 10nF 50V; C0805
C22: 2.2nF 50V; C0603
C23: 33nF 16V; C0603
C24: 220pF; C0805
C26: DE2E3KY222MA2BM01; AR21AC103K4R
CM1: 20mH CM CHOKE; WE-CMB_XS_744821120
CON1: 2X7
D1: MBRA340T3G; SMA
D2, D3, D4, D5, D6, D7, D8: MBRA340T3; SMA
D15: MRA4007T3G; SMA
D16: STPS5H100B; DPAK_STM
D17, D18, D19: BAT41ZFILM; SOD-123_MINI-SMA
D20: MMSZ5248B-V-GS08; DO214AC
F2: 696101000002
IC1: ULN2803A; SO18
IC3: TS432ILT; SOT23
IC4: VIPER35HD
L2: 3.3uH SD43-332ML; INDUCTOR-BOURNS_SRN8040
OPT2: SFH6106-2T; SMD-4_SFH610X_VIS-M
R1, R2, R3, R4, R5, R6, R7, R8: 330R 1W; 1206
R9, R10: 0R; 0805
R13: 220K 5% 0.33W 200V; 1206
R14: 1K; 0603
R15: 12K; 0603
R16: 82K; 0603
R17: 130K 1%; 0603
R18: 15K 1%; 0603
R19: 4.7R 1%; 0603
R20: 330K 1%; 0603
R21: 133K 1%; 0603
R22: 30K 1%; 0603
R23: 47K 1%; 0603
R24: 220R; 0805
REL1, REL2, REL3, REL4, REL5, REL6, REL7, REL8: G2RL-1A-E_DC12; RELAY_G2RL-1A-E_DC5_OMR
RV1: B72210S0321K101; WE-VD_10MM_820412001
T1: 750370228; WE-OLSTM_EE20_L22.2W25H16
U$1, U$2: ESD_10.00

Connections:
+12V: CON1.14, D1.C, D2.C, D3.C, D4.C, D5.C, D6.C, D7.C, D8.C, IC1.10, R9.1, R10.1, REL1.8, REL2.8, REL3.8, REL4.8, REL5.8, REL6.8, REL7.8, REL8.8
AC_LINE: F2.1, REL1.3, REL1.6, REL2.3, REL2.6, REL3.3, REL3.6, REL4.3, REL4.6, REL5.3, REL5.6, REL6.3, REL6.6, REL7.3, REL7.6, REL8.3, REL8.6
AC_LINE2: C14.2, CM1.1, RV1.2
AGND: BR1.-, C15.2, C17.2, C22.2, C24.2, C25.2, C26.1, D17.A, D20.A, IC4.1, IC4.2, IC4.3, IC4.4, IC4.8, OPT2.4, R22.2, R23.2, T1.3
DC_RAW: BR1.+, C15.1, C16.1, C17.1, R13.2, T1.6
FB: C22.1, C23.1, IC4.7, OPT2.3
GND: C18.2, C19.2, C20.2, C26.2, CON1.13, IC1.9, IC3.3, R18.2, T1.10
unnamed: C19.1, C20.1, L2.2, R9.2, R10.2, R17.1
unnamed: BR1.AC1, CM1.4
unnamed: IC1.18, R1.1
unnamed: IC1.17, R2.1
unnamed: IC1.16, R3.1
unnamed: IC1.15, R4.1
unnamed: IC1.14, R5.1
unnamed: IC1.13, R6.1
unnamed: BR1.AC2, CM1.3
unnamed: IC1.12, R7.1
unnamed: IC1.11, R8.1
unnamed: C14.1, CM1.2, F2.2, RV1.1
unnamed: C16.2, D15.C, R13.1
unnamed: D15.A, IC4.13, IC4.14, IC4.15, IC4.16, T1.4
unnamed: D16.2, T1.8
unnamed: C18.1, D16.3, L2.1, R14.1
unnamed: IC3.2, OPT2.1, R14.2, R15.1
unnamed: OPT2.2, R15.2, R16.1
unnamed: C21.1, R16.2
unnamed: C21.2, IC3.1, R17.2, R18.1
unnamed: C24.1, C25.1, D19.C, IC4.5, R24.1
unnamed: D19.A, R19.2
unnamed: D18.A, R19.1, R20.1, T1.1
unnamed: D17.C, D18.C, R21.1
unnamed: IC4.6, R20.2, R21.2, R22.1
unnamed: C23.2, R23.1
unnamed: D20.C, R24.2
OUT_1: REL1.4, REL1.5
OUT_2: REL2.4, REL2.5
OUT_3: REL3.4, REL3.5
OUT_4: REL4.4, REL4.5
OUT_5: REL5.4, REL5.5
OUT_6: REL6.4, REL6.5
OUT_7: REL7.4, REL7.5
OUT_8: REL8.4, REL8.5
RELAY_1: D1.A, R1.2, REL1.1
RELAY_2: D2.A, R2.2, REL2.1
RELAY_3: D3.A, R3.2, REL3.1
RELAY_4: D4.A, R4.2, REL4.1
RELAY_5: D5.A, R5.2, REL5.1
RELAY_6: D6.A, R6.2, REL6.1
RELAY_7: D7.A, R7.2, REL7.1
RELAY_8: D8.A, R8.2, REL8.1
REL_0: CON1.12, IC1.1
REL_1: CON1.11, IC1.2
REL_2: CON1.10, IC1.3
REL_3: CON1.9, IC1.4
REL_4: CON1.8, IC1.5
REL_5: CON1.7, IC1.6
REL_6: CON1.6, IC1.7
REL_7: CON1.5, IC1.8

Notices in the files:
parts and their libraries:
Wurth_Switch_WS-TASV: Copyright: Würth Elektronik
COPYRIGHT: Copyright (C) 2025 Ultra Librarian. All rights reserved.
